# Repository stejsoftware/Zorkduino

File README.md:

# Zorkduino 

## links

* http://inform-fiction.org/zmachine/standards/z1point1/index.html

### Play Zork on your TV with an Arduino.

Who doesn’t love Zork?. Who doesn’t love Arduinos? Why not grab a few cheap components and build an Arduino gadget capable of playing all the classic Infocom games on your TV from the comfort of your couch.

A few years ago I ported a Z-Machine player to a [little arduino-like device](http://rossumblog.com/2011/04/19/zork-for-the-microtouch/). Ever since I have been meaning to get around to a project that would work on a TV with a real keyboard and once again rekindle fond memories of long nights playing Zork on my Atari 800.

### You will need:

* Arduino UNO, Pro, Pro Mini or equivalent.
* SD card or micro SD card + breakout board (from Adafruit, eBay etc).
* RCA A/V Cable (eBay).
* 470ohm, 1k and 100k resistors.
* Breadboard, wires etc.
* WebTV or MsnTV IR Keyboard or PS2 a nasty old PS2 keyboard (eBay).
* IR receiver TSOP38238,TSOP4838 or equivalent (Adafruit, Mouser etc).

## Building it

The schematic is very simple:

```
        +----------------+           +-----------------+
        |                |           |                 |
        |             13 |-----------| SCK    micro\SD |
        |             12 |-----------| MISO   card     |
        |             11 |-----------| MOSI   module   |
        |             10 |-----------| CS              |
        |                |      5v <-|                 |
        |                |     GND <-|                 |
        |    arduino     |           +-----------------+
        |    uno/pro     |
        |                |       5v <--+-+   IR Receiver
        |                |      GND <--|  )  TSOP4838 etc.
        |              8 |-------------+-+
        |                |
        |              6 |----[ 100k ]--------> AUDIO
        |                |
        |              9 |----[  1k  ]----+---> VIDEO
        |                |                |
        |              1 |----[ 470  ]----+
        |                |
        |              3 |----------------> *PS2 CLOCK
        |              2 |----------------> *PS2 DATA
        |                |
        +----------------+
```
### Layout on an Arduino Uno...

### ...and on a Mini Pro.

Just about any SD card or microsd card breakout will do. Some of the very cheap ones (<$1) don't have 5v to 3v3 level converters and may fry your SD card so caveat emptor. As always, Adafruit has nice ones.

WebTV keyboards come in various guises: WebTV, MsnTV, Displayer, UltimateTV etc. They all should work just fine. A few places have the nice Philips variant new for $11.95 w/ free shipping (search for 'SWK-8630'). This one comes with a nice PS2 IR receiver; more on it later.

IR receivers come in a number of different forms. You are looking for a 38khz version with a known pinout: Some have the center pin as GND, some as V+. Make sure you know what kind you have. When in doubt, Adafruit.

I like using iPhone/iPod video cables for TV projects. Because they no longer work (their MFI chip long since revoked) they are inexpensive, are labeled internally and have a strain relief grommet.

If you have an IR keyboard then good for you. If not, connect your nasty old PS2 clock and data lines to pins 3 and 2 then order an IR keyboard.

### On the disk

The [`stories`](stories) folder contains a `zd.mem` pagefile along with several sample games:

`tutorial.z3` Introduction to interactive fiction and a little bit of Zork I

`sampler1.z5`
Samples of Planetfall, Infidel, and The Witness.

`sampler2.z3`
Samples of  Zork I, Leather Goddesses of Phobos, and Trinity

`minizork.z3`
A nice big chunk of Zork I that was given away with the British Commodore users' magazine "Zzap! 64" no. 67. in 1990.

Copy these files to a freshly formatted sd or microsd card. You can find lots of other Zorkduino compatible games at the [Interactive Fiction Archive](http://www.ifarchive.org/). Insert the card and run the `zorkduino.ino` sketch from the [`zorkduino`](.) folder. When it is all up and running, it should look like this (depending on how many games you found):

## How it works

Squeezing Zork into the limited footprint of an Arduino proved to be a bit of a challenge. The code uses a port of Mark Howell and John Holder's JZIP, a Z-machine interpreter. The Z-machine was created in 1979 to play large (100k!) adventure games on small (8K!) personal computers. Long before Java the implementors at Infocom built a virtual machine capable of paging, loading and saving complete runtime state that ran on a wide variety of CPUs. Clever stuff.

The trouble is the Arduino only has 2k of ram. The Z-machine interpreter uses 2k for its stack alone, leaving no room for dynamic memory, disk buffers, video frame buffers, avr stack and other program state. The solution is to virtualize all stack and memory accesses from the interpreter down to a 160 byte cache and a 512 byte disk buffer. Thats where the `zd.mem` file comes in - a megabyte or so of virtual stack, memory and save-game slots.

Virtualizing everything slows things down a bit but serendipitously makes the Arduino perform at roughly the same speed as my old Atari 800. Video needs 912 bytes for the frame buffer, leaving ~464 bytes for the avr stack and all application and interpreter state.

### Video

The video is generated with a simple state machine on the Timer1 ISR. HSYNC interrupts occur at 15.73kHz and trigger state changes for video, audio and keyboard state machines.

Active video is 308x192 pixels, 38x24 8x8 charaters. Getting this resolution requires use of the UART in SPI mode running at top (8Mhz) speed to shift out pixels from either a character font (the Atari 800 default font) or a graphics font (an extravagant waste of 2k logo). Because the video is being emitted from the TX pin it is fun to open the serial monitor to watch what ntsc video looks like as text: almost at bit Matrixy.

### Audio

No homage to 70's and 80's computing would be complete without keyboard beeps and disk thweeps. Keystrokes generate a 1000hz feedback beep, sd card writes make a 3600hz mechanical click. These sounds are generated in the video isr by toggling pin 6 after a certain number of HSYNCs.

### Keyboard

WebTV IR is an unusual UART-like asych serial protocol. It runs at ~660 baud with 3.25 start bits, a 10 bit class code, 8 bit key code, parity and stop bit. Class codes are things like keyup, keydown etc. and key codes map physical keyboard layout. The video ISR counts HSYNCs between transitions on the IR data line and passes state change events to the keyboard code. 

The PS2 code is pretty conventional. A good explanation is [here](http://www.computer-engineering.org/ps2protocol/).

## Extra Credit

If you get the Philips $11.95 keyboard variant you get a PS2 IR receiver as well. The receiver can be...

* used as-is as a PS2 keyboard connected to pins 2 and 3.
* gutted and turned into a nice case.

I prefer the latter. The case has a nice slot in the back with a sliding door that is perfect for a microSD card. It has a nice IR window at the front and a TSOP31238 (5V center pin) IR receiver that can be harvested from the PCB. Get a cheap Pro/Mini + microsd breakout, add that iPod video cable and it looks like this:

Drop me a line at rossumur@gmail.com if you have any trouble.

cheers

[rossumblog.com](http://rossumblog.com)

p.s. The maze in minizork is not the same layout as in Zork I. I have it if you need it.

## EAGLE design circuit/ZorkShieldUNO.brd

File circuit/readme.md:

# Zorkduino Shield

Eagle schematics and PCB for a Shield compatible with Arduino UNO. It features:

* PS/2 keyboard connector
* USB-A female, alternative mount for USB keyboards that can revert to PS/2 mode
* SD Card Connector
* Micro SD (alternative mount) Card Connector
* Dual RCA connector for Audio/Video
* P2 Stereo Jack (alternative mount) for Audio/Video 
* Infrared Receiver
* Reset Button

The connectors were disposed so all the wired connections are on the same side while the SD 
socket and the Infrared receiver are on the opposite side. This should make the device more
easy to be used and hence easier to put in a box.

The board was manually routed.

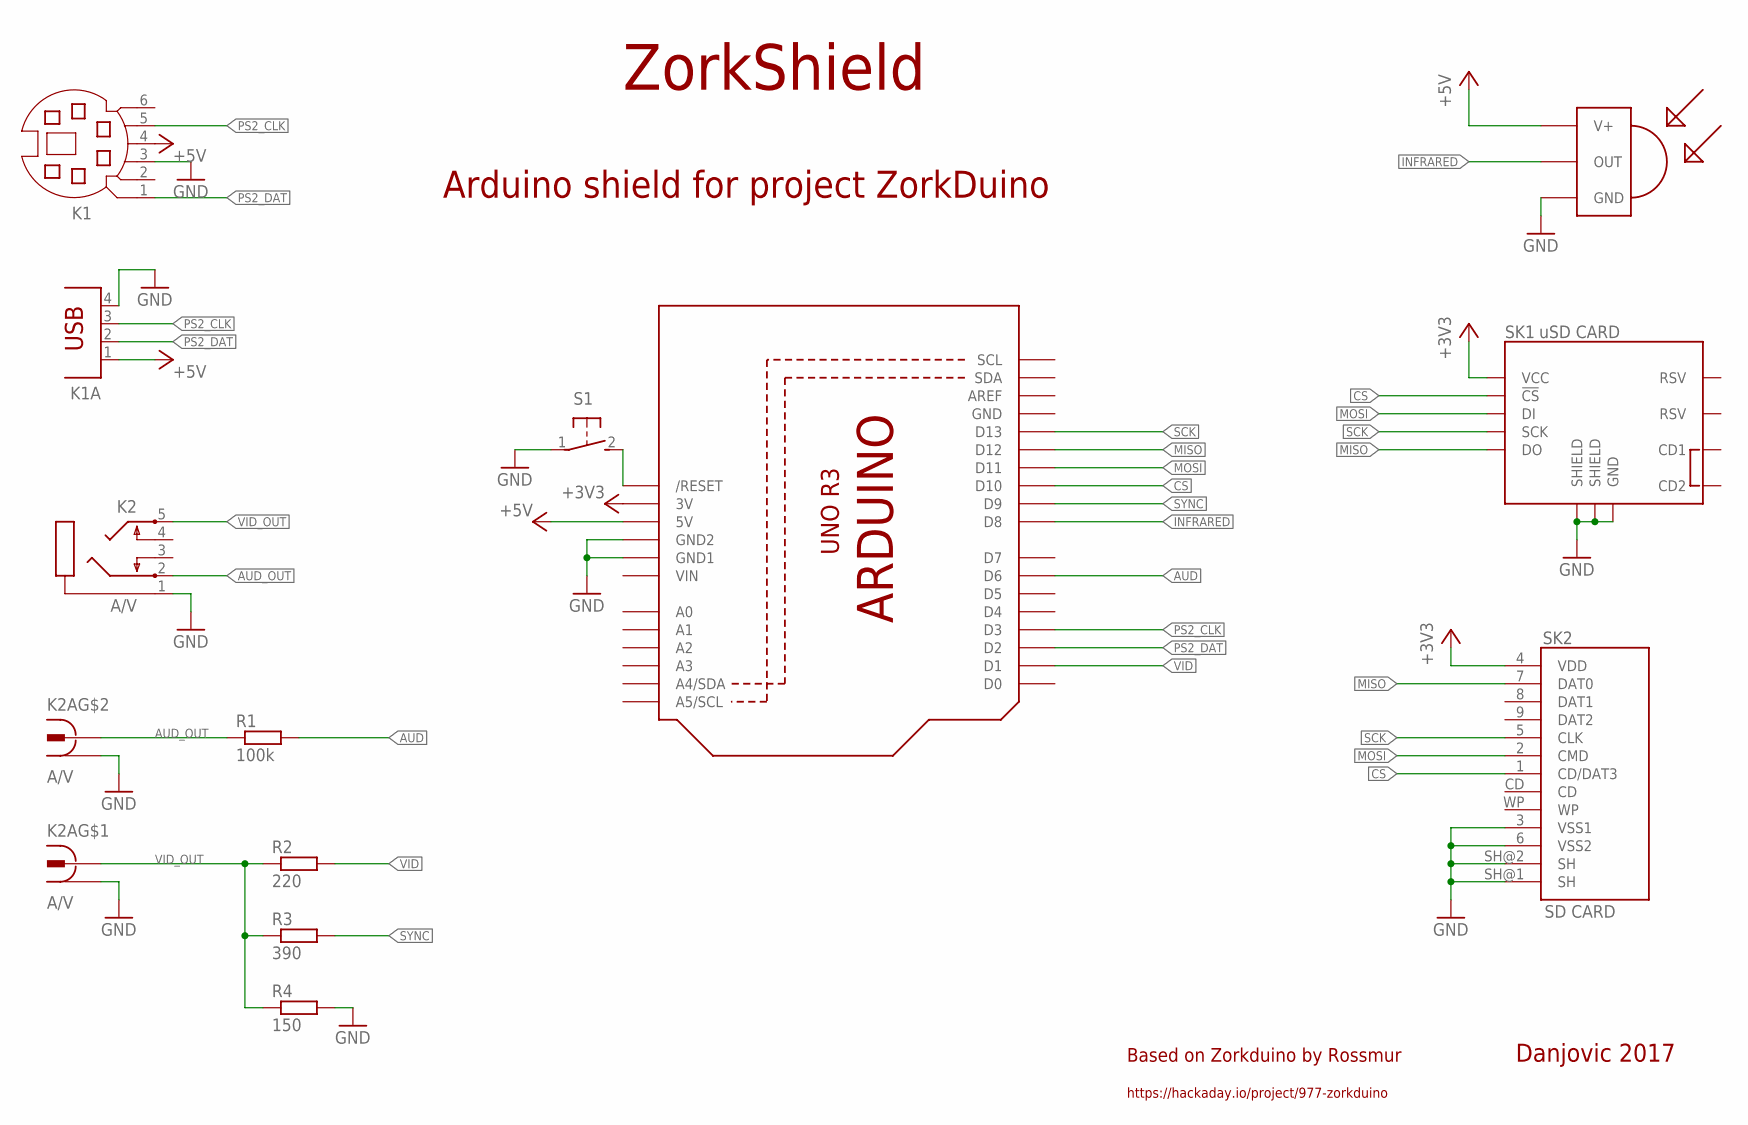
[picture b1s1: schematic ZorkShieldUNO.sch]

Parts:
IR1: TSOP4837; TSOP18XX
K1: MD06SS; MDIN06SS
K1A: PN87520
K2: A/V; PG203J
K2A: A/V; DOUBLE_VERTICAL_2
Q1: ARDUINOR3-NOIOREF-NOTEXT; ARDUINOR3-NOTEXT-NOIOREF
R1: 100k; 0204/7
R2: 220; 0204/7
R3: 390; 0204/7
R4: 150; 0204/7
S1: 31-XX; B3F-31XX
SK1: uSD CARD; MICRO-SD-SOCKET-PP
SK2: SD CARD; SDCARD_4UCONN

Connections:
+3V3: Q1.3V, SK1.VCC, SK2.4 (VDD)
+5V: IR1.VCC (V+), K1.4, K1A.1, Q1.5V
AUD: Q1.D6, R1.2
AUD_OUT: K2.2, K2A.LS (2), R1.1
CS: Q1.D10, SK1.CS (!CS), SK2.1 (CD/DAT3)
GND: IR1.GND, K1.3, K1A.4, K2.1, K2A.HG (1), K2A.LG (1), Q1.GND, Q1.GND1, Q1.GND2, R4.2, S1.1, SK1.GND, SK1.GND1 (SHIELD), SK1.GND3 (SHIELD), SK2.3 (VSS1), SK2.6 (VSS2), SK2.SH@1 (SH), SK2.SH@2 (SH)
INFRARED: IR1.OUT, Q1.D8
MISO: Q1.D12, SK1.DO, SK2.7 (DAT0)
MOSI: Q1.D11, SK1.DI, SK2.2 (CMD)
unnamed: Q1.RESET (/RESET), S1.2 (S)
PS2_CLK: K1.5, K1A.3, Q1.D3
PS2_DAT: K1.1, K1A.2, Q1.D2
SCK: Q1.D13, SK1.SCLK (SCK), SK2.5 (CLK)
SYNC: Q1.D9, R3.2
VID: Q1.D1, R2.2
VID_OUT: K2.5, K2A.HS (2), R2.1, R3.1, R4.1
VIN: Q1.VIN

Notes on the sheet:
Arduino shield for project ZorkDuino
ZorkShield
Based on Zorkduino by Rossmur
Danjovic 2017
https://hackaday.io/project/977-zorkduino

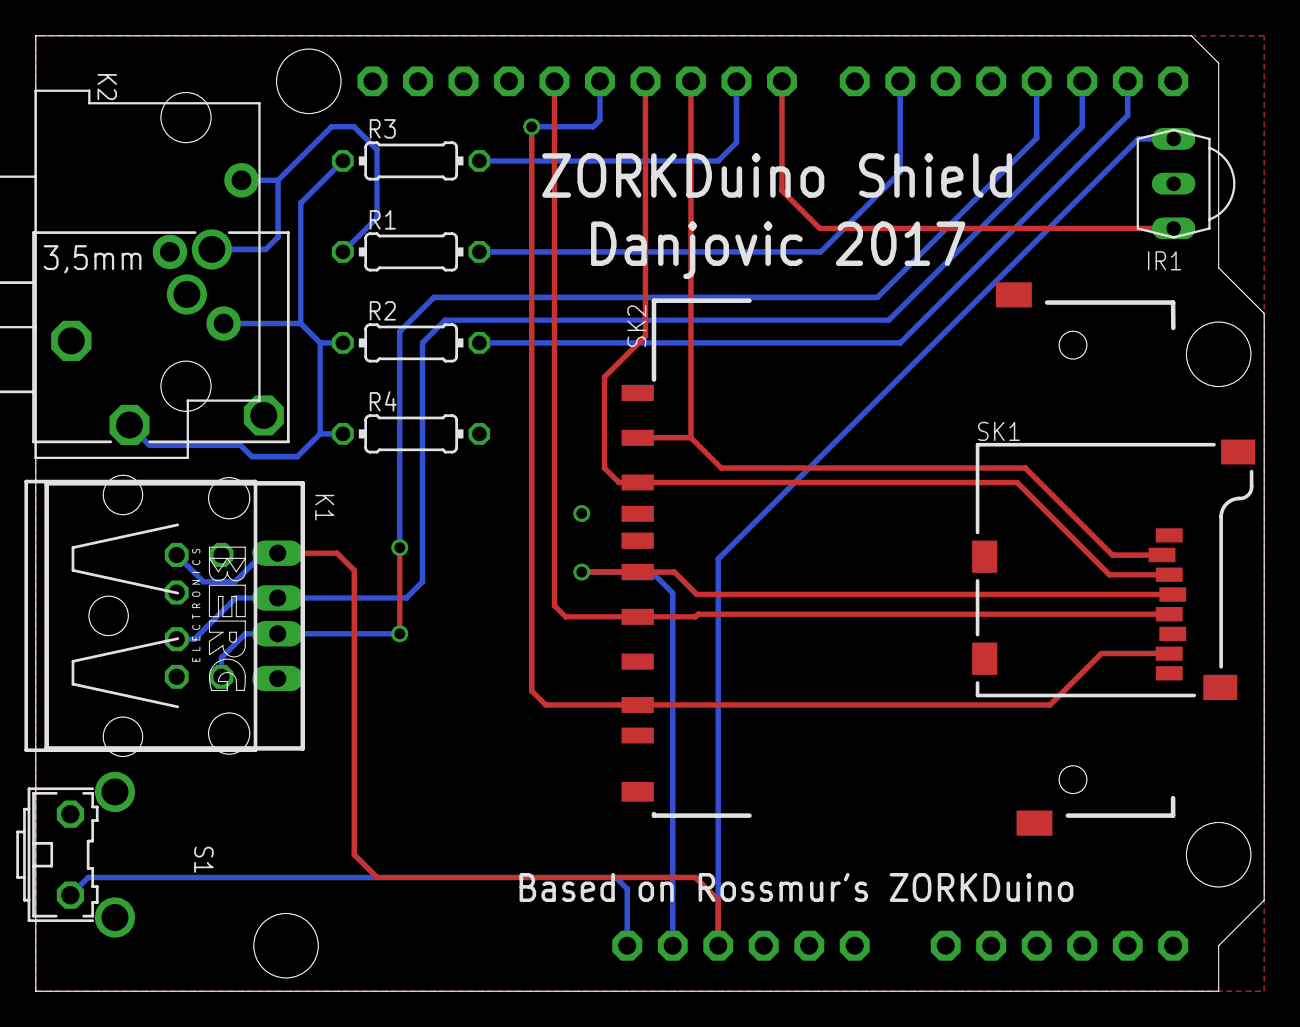
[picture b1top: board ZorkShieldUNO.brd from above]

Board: 2 copper layers, 68.6 x 53.3 mm, 13 parts (0 on the bottom side), 16 nets.

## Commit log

2017-03-12 Create Readme.md for Eagle files
2017-03-12 Added Eagle files for the Zorkduino shield
2018-03-18 moving files around
2018-03-18 move
2018-03-18 cleanup
2018-03-18 Convert to a PlatformIO project.
2018-03-18 added support for pro-mini and trinket
2018-04-22 moving to a zmachine library

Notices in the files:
parts and their libraries:
SparkFun-Connectors: Licensing: Creative Commons ShareAlike 4.0 International - https://creativecommons.org/licenses/by-sa/4.0
